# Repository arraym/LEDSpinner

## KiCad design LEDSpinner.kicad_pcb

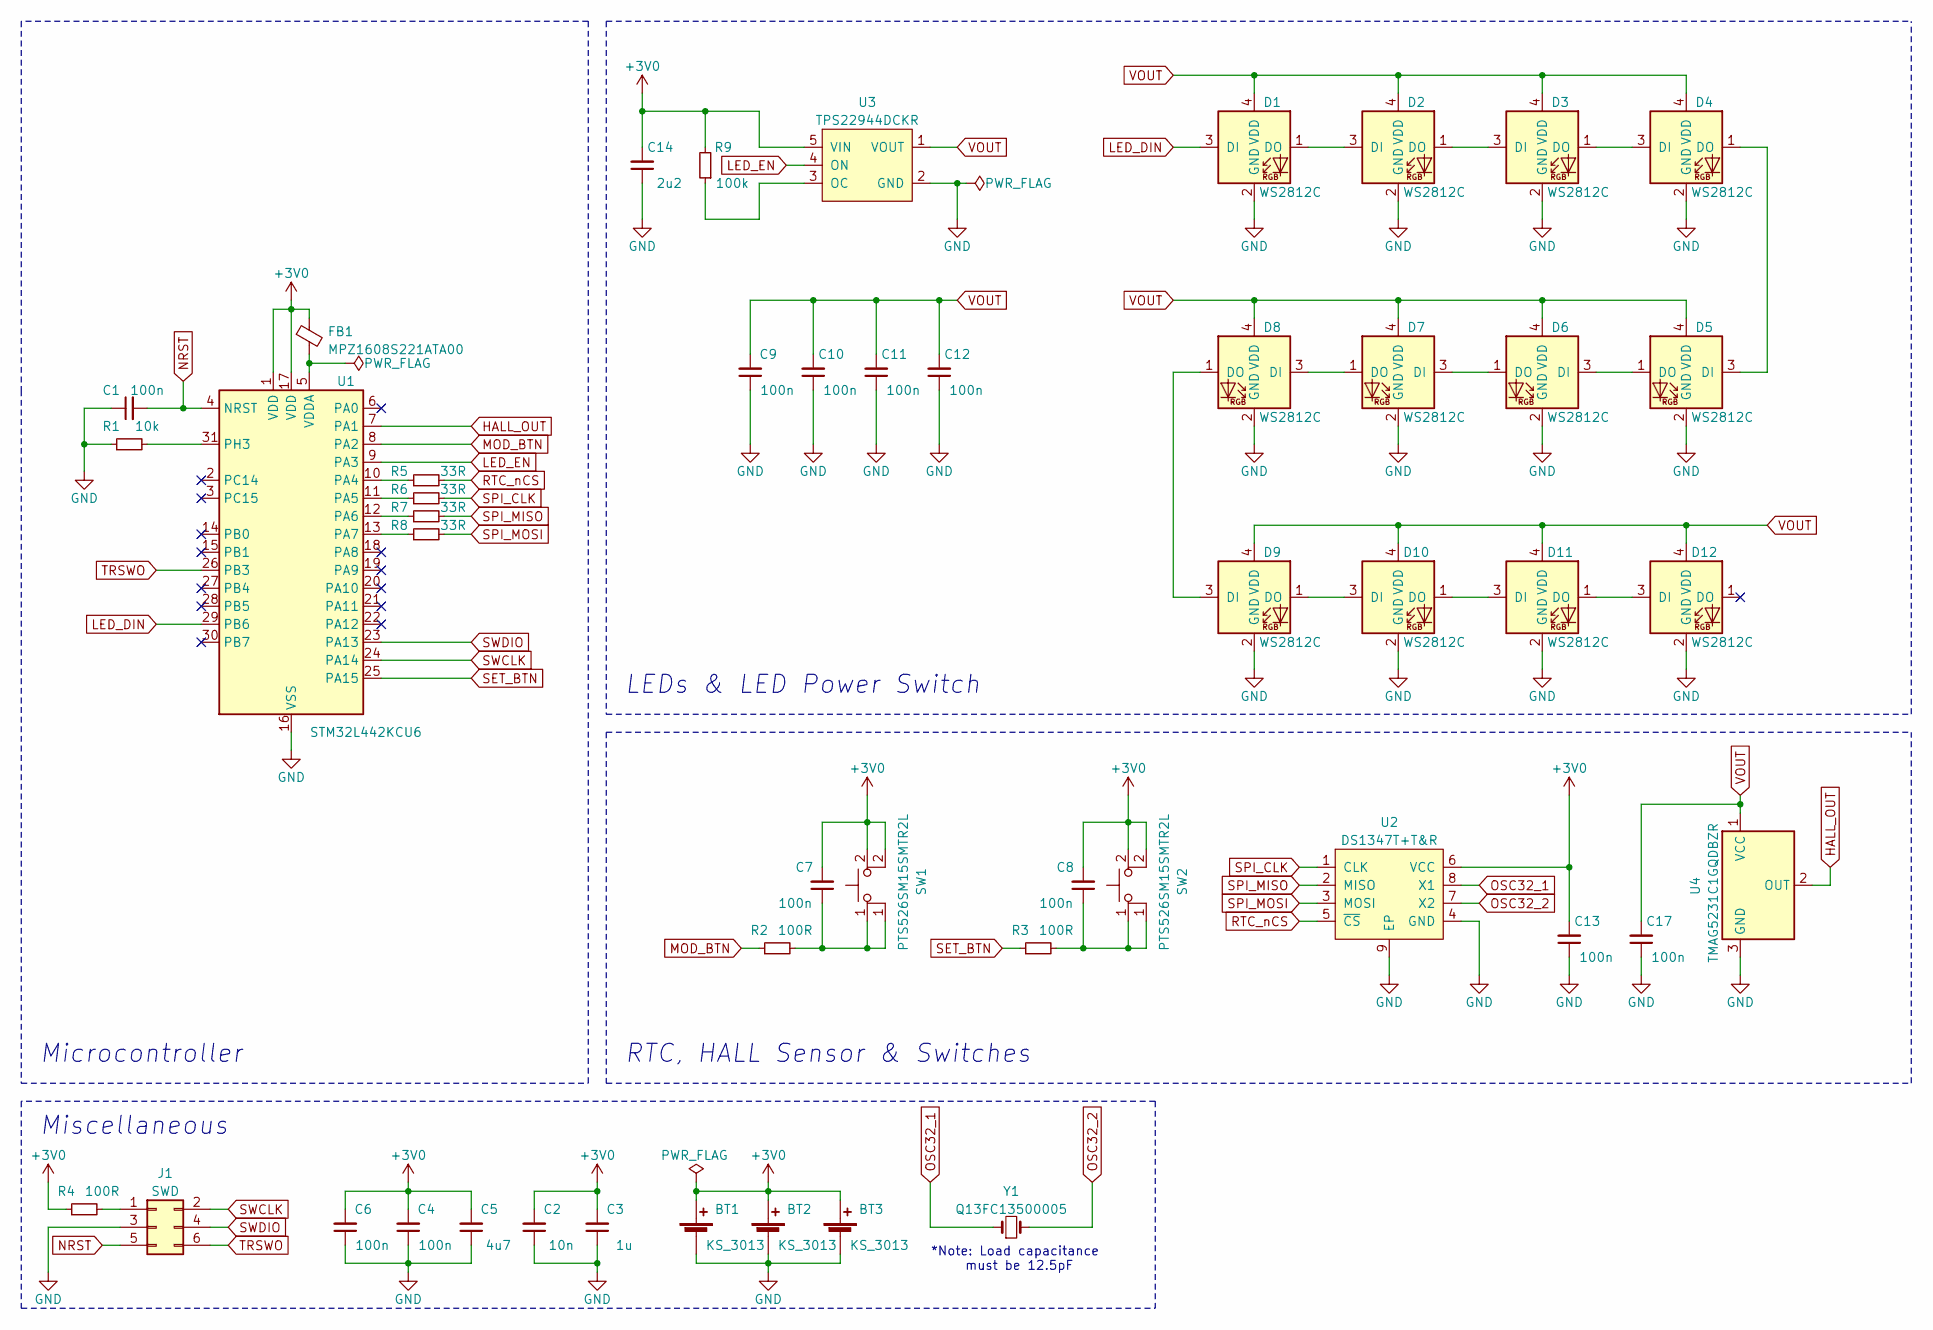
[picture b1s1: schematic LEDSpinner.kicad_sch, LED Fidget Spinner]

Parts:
BT1, BT2, BT3: KS_3013; BatteryHolder_Keystone_3013_1x1632_THT
C1, C4, C6, C7, C8, C9, C10, C11, C12, C13, C17: 100n; C_0603_1608Metric_Pad1.08x0.95mm_HandSolder
C2: 10n; C_0603_1608Metric_Pad1.08x0.95mm_HandSolder
C3: 1u; C_0603_1608Metric_Pad1.08x0.95mm_HandSolder
C5: 4u7; C_0603_1608Metric_Pad1.08x0.95mm_HandSolder
C14: 2u2; C_0603_1608Metric_Pad1.08x0.95mm_HandSolder
D1, D2, D3, D4, D5, D6, D7, D8, D9, D10, D11, D12: WS2812C; WS2812-2020
FB1: MPZ1608S221ATA00; L_0603_1608Metric_Pad1.05x0.95mm_HandSolder
J1: SWD; TC2030-MCP-NL
R1: 10k; R_0603_1608Metric_Pad0.98x0.95mm_HandSolder
R2, R3, R4: 100R; R_0603_1608Metric_Pad0.98x0.95mm_HandSolder
R5, R6, R7, R8: 33R; R_0603_1608Metric_Pad0.98x0.95mm_HandSolder
R9: 100k; R_0603_1608Metric_Pad0.98x0.95mm_HandSolder
SW1, SW2: PTS526SM15SMTR2L; SW_SPST_TL3342
U1: STM32L442KCU6; QFN-32-1EP_5x5mm_P0.5mm_EP3.45x3.45mm
U2: DS1347T+T&R; DFN-8-1EP_3x3mm_P0.65mm_EP1.55x2.4mm
U3: TPS22944DCKR; SOT-353_SC-70-5
U4: TMAG5231C1GQDBZR; SOT-23
Y1: Q13FC13500005; Crystal_SMD_Abracon-2Pin_3.2x1.5mm

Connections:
+3V0: BT1.1 (+), BT2.1 (+), BT3.1 (+), C2.2, C3.2, C4.2, C5.2, C6.2, C7.2, C8.2, C13.2, C14.2, FB1.1, R4.1, R9.2, SW1.2, SW2.2, U1.1 (VDD), U1.17 (VDD), U2.6 (VCC), U3.5 (VIN)
GND: BT1.2 (-), BT2.2 (-), BT3.2 (-), C1.1, C2.1, C3.1, C4.1, C5.1, C6.1, C9.1, C10.1, C11.1, C12.1, C13.1, C14.1, C17.1, D1.2 (GND), D2.2 (GND), D3.2 (GND), D4.2 (GND), D5.2 (GND), D6.2 (GND), D7.2 (GND), D8.2 (GND), D9.2 (GND), D10.2 (GND), D11.2 (GND), D12.2 (GND), J1.3, R1.1, U1.16 (VSS), U1.32 (VSS), U1.33 (VSS), U2.4 (GND), U2.9 (EP), U3.2 (GND), U4.3 (GND); also elsewhere on the board
HALL_OUT: U1.7 (PA1), U4.2 (OUT)
LED_DIN: D1.3 (DI), U1.29 (PB6)
LED_EN: U1.9 (PA3), U3.4 (ON)
MOD_BTN: R2.1, U1.8 (PA2)
NRST: C1.2, J1.5, U1.4 (NRST)
unnamed: FB1.2, U1.5 (VDDA)
unnamed: C7.1, R2.2, SW1.1
unnamed: C8.1, R3.2, SW2.1
unnamed: D1.1 (DO), D2.3 (DI)
unnamed: D2.1 (DO), D3.3 (DI)
unnamed: D3.1 (DO), D4.3 (DI)
unnamed: D4.1 (DO), D5.3 (DI)
unnamed: D5.1 (DO), D6.3 (DI)
unnamed: D6.1 (DO), D7.3 (DI)
unnamed: D7.1 (DO), D8.3 (DI)
unnamed: D8.1 (DO), D9.3 (DI)
unnamed: D9.1 (DO), D10.3 (DI)
unnamed: D10.1 (DO), D11.3 (DI)
unnamed: D11.1 (DO), D12.3 (DI)
unnamed: J1.1, R4.2
unnamed: R5.1, U1.10 (PA4)
unnamed: R6.1, U1.11 (PA5)
unnamed: R7.1, U1.12 (PA6)
unnamed: R8.1, U1.13 (PA7)
unnamed: R1.2, U1.31 (PH3)
unnamed: R9.1, U3.3 (OC)
OSC32_1: U2.8 (X1), Y1.1
OSC32_2: U2.7 (X2), Y1.2
RTC_nCS: R5.2, U2.5 (~CS)
SET_BTN: R3.1, U1.25 (PA15)
SPI_CLK: R6.2, U2.1 (CLK)
SPI_MISO: R7.2, U2.2 (MISO)
SPI_MOSI: R8.2, U2.3 (MOSI)
SWCLK: J1.2, U1.24 (PA14)
SWDIO: J1.4, U1.23 (PA13)
TRSWO: J1.6, U1.26 (PB3)
VOUT: C9.2, C10.2, C11.2, C12.2, C17.2, D1.4 (VDD), D2.4 (VDD), D3.4 (VDD), D4.4 (VDD), D5.4 (VDD), D6.4 (VDD), D7.4 (VDD), D8.4 (VDD), D9.4 (VDD), D10.4 (VDD), D11.4 (VDD), D12.4 (VDD), U3.1 (VOUT), U4.1 (VCC)

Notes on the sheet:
*Note: Load capacitance must be 12.5pF
LEDs & LED Power Switch
Microcontroller
RTC, HALL Sensor & Switches
Miscellaneous

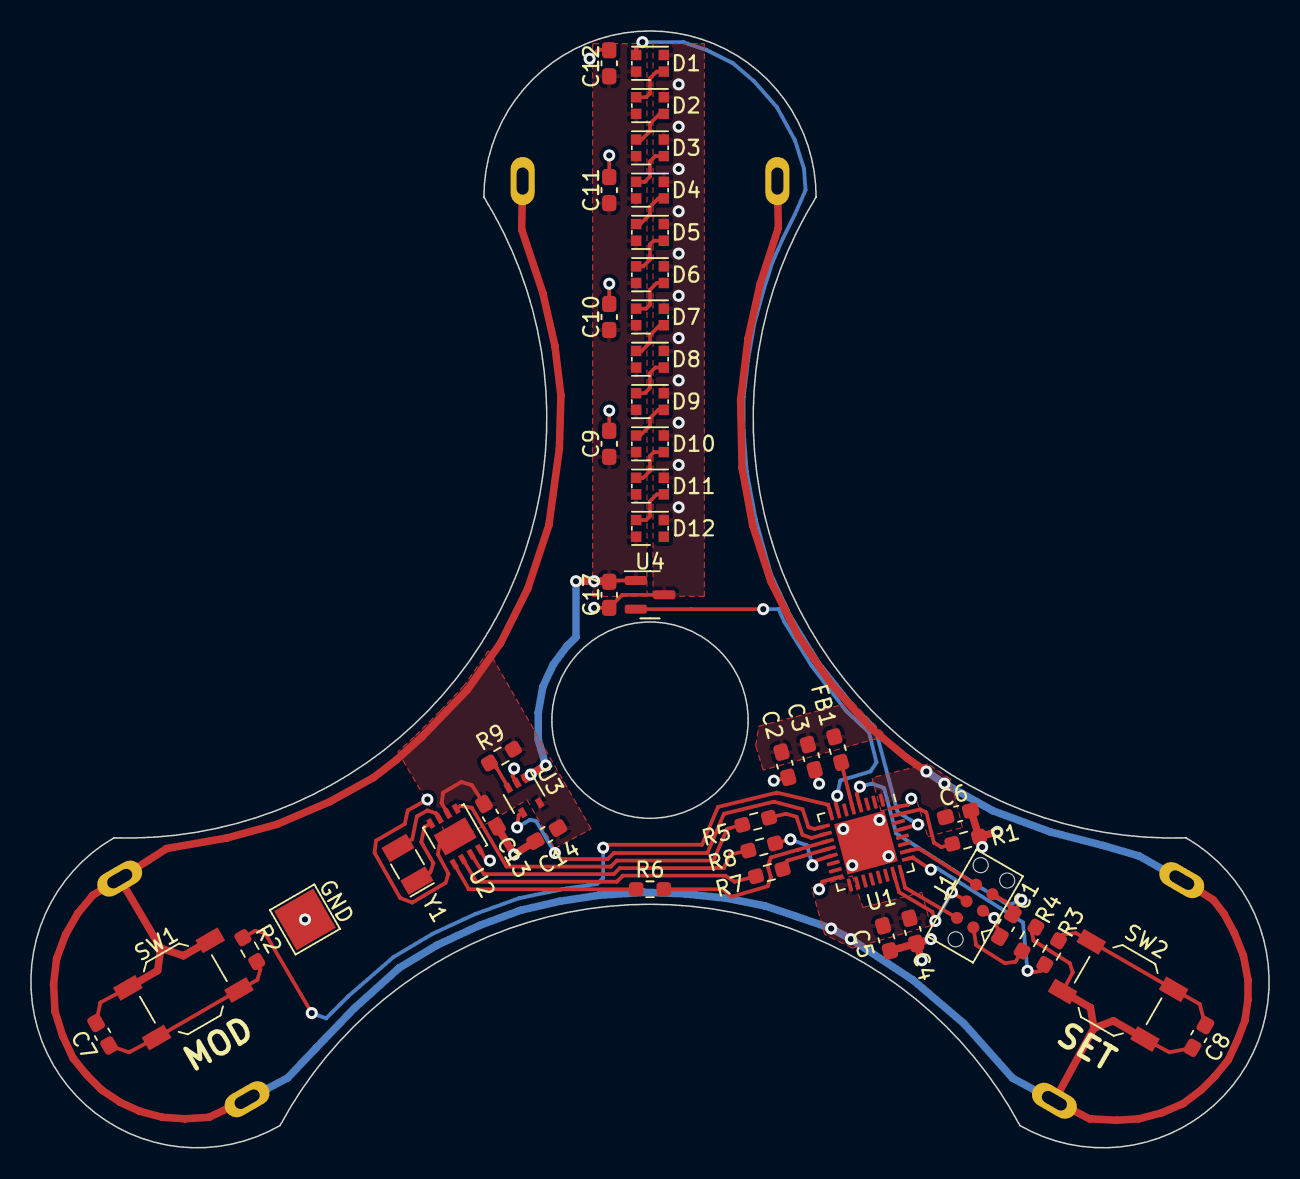
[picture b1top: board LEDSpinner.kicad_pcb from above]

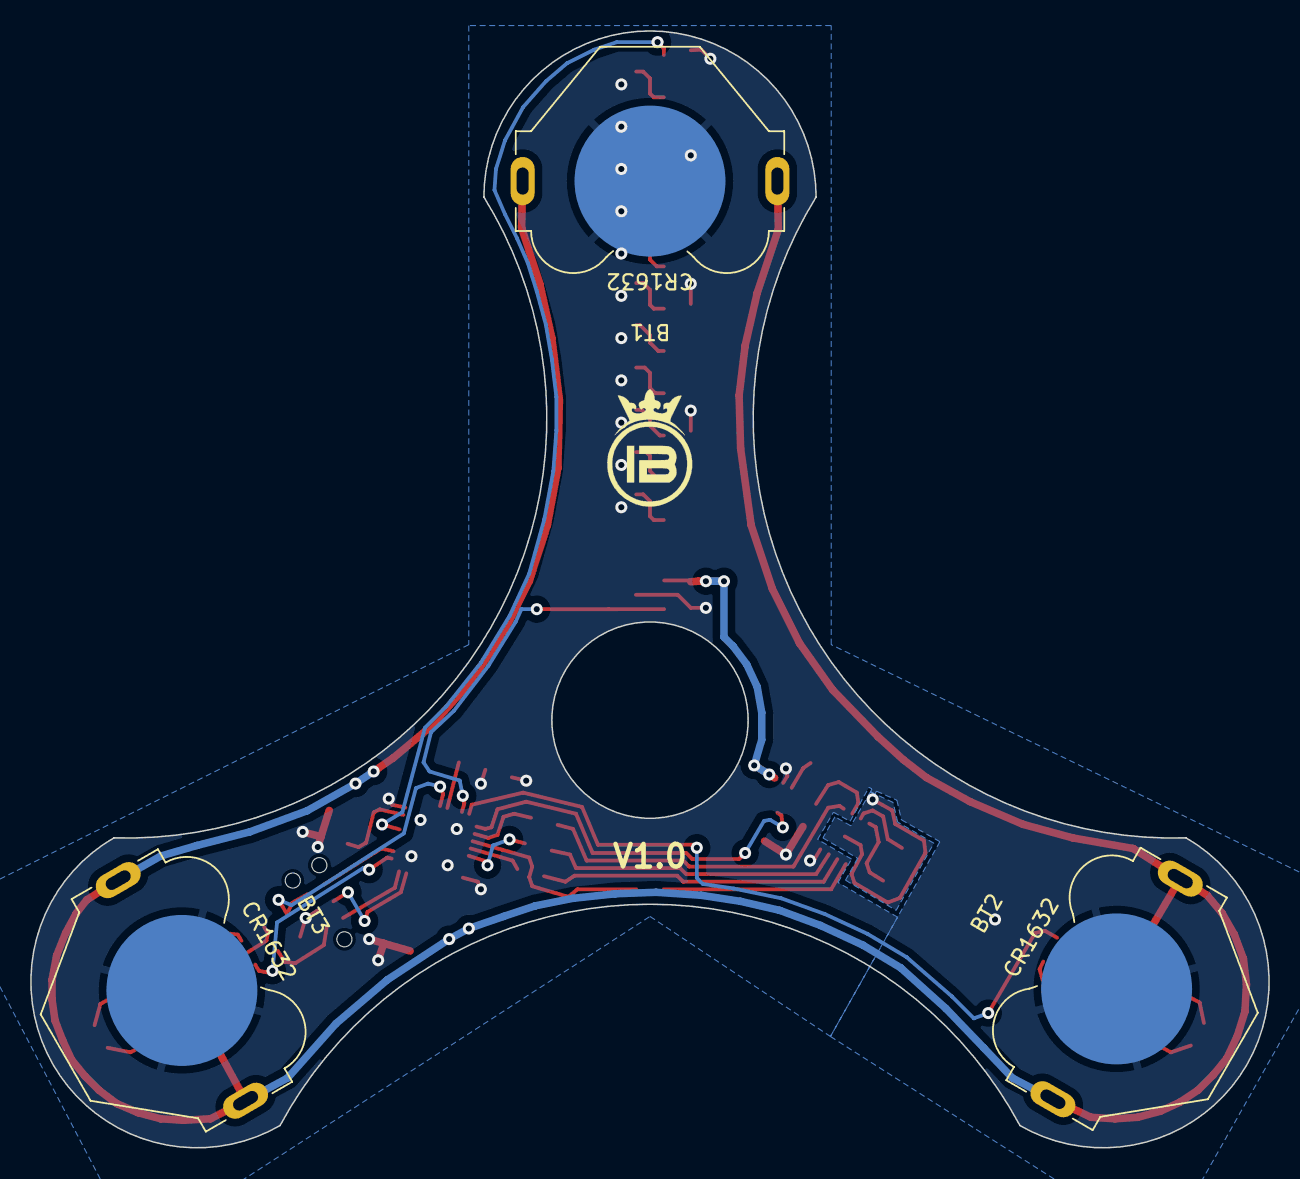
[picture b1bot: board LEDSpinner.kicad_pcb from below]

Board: 2 copper layers, 82.0 x 74.0 mm, 49 parts (3 on the bottom side), 39 nets.

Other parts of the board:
GND: TestPoint_Pad_3.0x3.0mm

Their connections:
GND: GND.1; also elsewhere on the board

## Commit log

2023-04-30 Initial commit.
2023-05-06 Production files updated.
